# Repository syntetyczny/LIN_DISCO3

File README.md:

##LIN DISCO3 WBus webasto driver

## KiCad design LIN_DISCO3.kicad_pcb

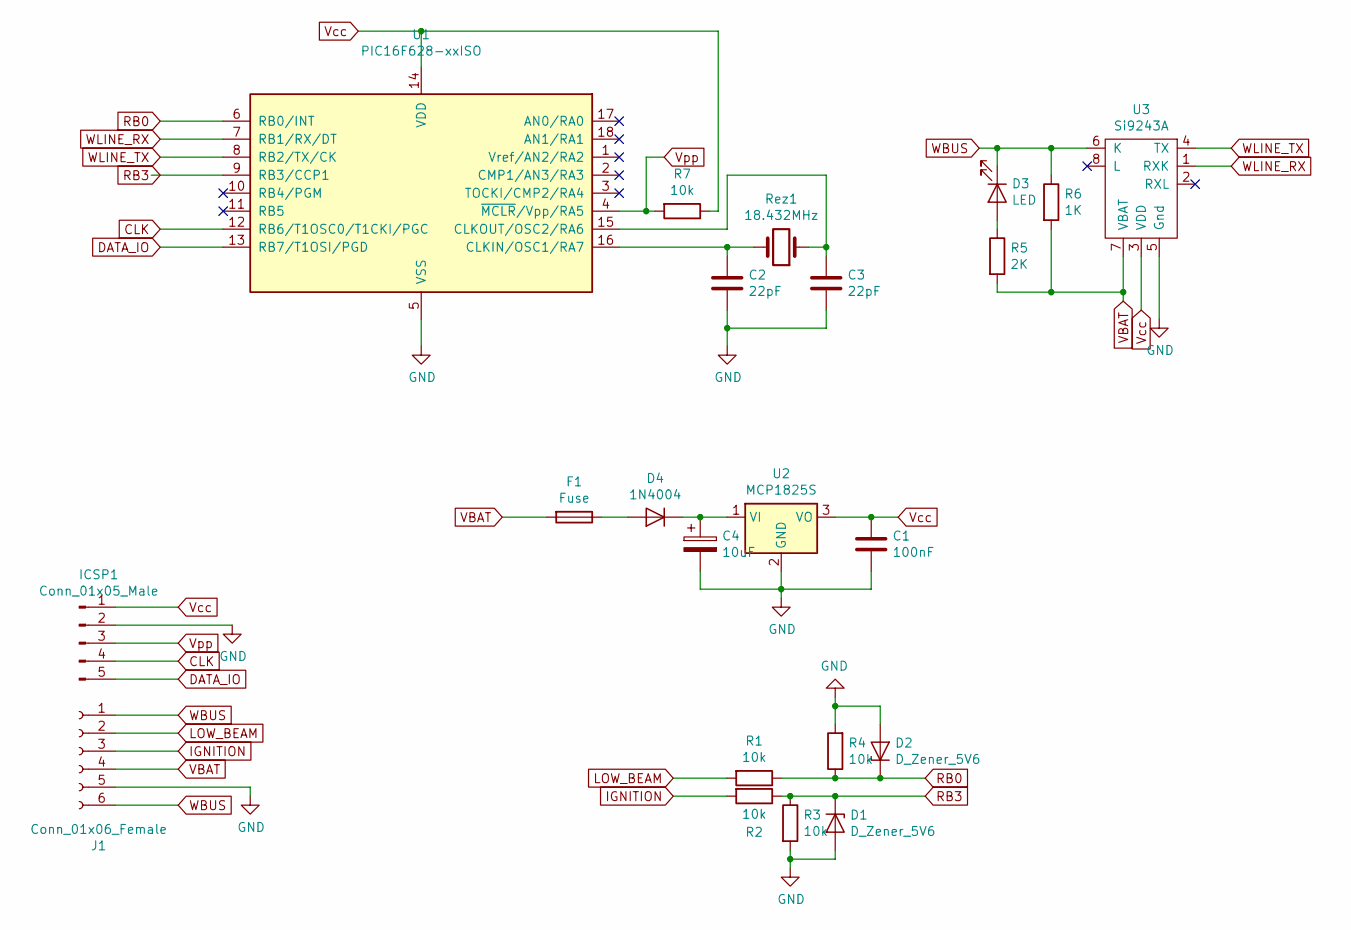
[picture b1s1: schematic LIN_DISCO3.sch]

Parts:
C1: 100nF; C_0805_2012Metric_Pad1.15x1.40mm_HandSolder
C2, C3: 22pF; C_0805_2012Metric_Pad1.15x1.40mm_HandSolder
C4: 10uF; CP_Elec_4x5.8
D1, D2: D_Zener_5V6; D_MiniMELF
D3: LED; LED_0805_2012Metric_Pad1.15x1.40mm_HandSolder
D4: 1N4004; D_SMB
F1: Fuse; Fuseholder_Cylinder-5x20mm_Stelvio-Kontek_PTF78_Horizontal_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
ICSP1: Conn_01x05_Male; PinHeader_1x05_P2.54mm_Vertical
J1: Conn_01x06_Female; TerminalBlock_Phoenix_PT-1,5-6-5.0-H_1x06_P5.00mm_Horizontal
R1, R2, R3, R4, R7: 10k; R_0805_2012Metric_Pad1.15x1.40mm_HandSolder
R5: 2K; R_0805_2012Metric_Pad1.15x1.40mm_HandSolder
R6: 1K; R_0805_2012Metric_Pad1.15x1.40mm_HandSolder
Rez1: 18.432MHz; Crystal_HC49-U_Vertical
U1: PIC16F628-xxISO; SOIC-18W_7.5x11.6mm_P1.27mm
U2: MCP1825S; SOT-223-3_TabPin2
U3: Si9243A; SOIC-8_3.9x4.9mm_P1.27mm

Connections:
CLK: ICSP1.4, U1.12 (RB6/T1OSC0/T1CKI/PGC)
DATA_IO: ICSP1.5, U1.13 (RB7/T1OSI/PGD)
GND: C1.2, C2.2, C3.2, C4.2, D1.2 (A), D2.2 (A), ICSP1.2, J1.5, R3.2, R4.2, U1.5 (VSS), U2.2 (GND), U3.5 (Gnd)
IGNITION: J1.3, R2.2
LOW_BEAM: J1.2, R1.2
unnamed: C2.1, Rez1.2, U1.16 (CLKIN/OSC1/RA7)
unnamed: C3.1, Rez1.1, U1.15 (CLKOUT/OSC2/RA6)
unnamed: C4.1, D4.1 (K), U2.1 (VI)
unnamed: D3.2 (A), R5.1
unnamed: D4.2 (A), F1.1
RB0: D2.1 (K), R1.1, R4.1, U1.6 (RB0/INT)
RB3: D1.1 (K), R2.1, R3.1, U1.9 (RB3/CCP1)
VBAT: F1.2, J1.4, R5.2, R6.2, U3.7 (VBAT)
Vcc: C1.1, ICSP1.1, R7.1, U1.14 (VDD), U2.3 (VO), U3.3 (VDD)
Vpp: ICSP1.3, R7.2, U1.4 (~MCLR~/Vpp/RA5)
WBUS: D3.1 (K), J1.1, J1.6, R6.1, U3.6 (K)
WLINE_RX: U1.7 (RB1/RX/DT), U3.1 (RXK)
WLINE_TX: U1.8 (RB2/TX/CK), U3.4 (TX)

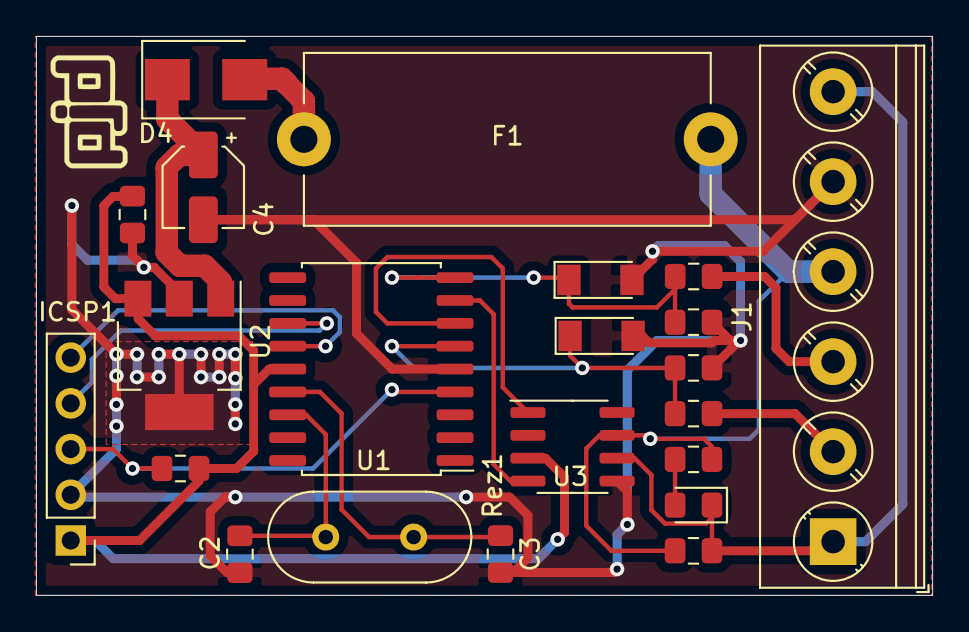
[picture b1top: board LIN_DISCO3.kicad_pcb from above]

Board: 2 copper layers, 49.8 x 31.1 mm, 22 parts (0 on the bottom side), 18 nets.

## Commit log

2022-01-23 shematic and docs init
2022-01-24 schematic: draft
2022-01-26 reroute, added 6p arks
2022-01-26 reroute: voltages
2022-01-26 added ICSP port
2022-02-12 transceiver changed to transistor cascade
2022-02-15 diodes and transistors case changed
2022-02-15 updated board for sot23 and miniMELF
2022-02-15 board layout prepared for production
2022-02-15 Added README.md
2022-03-08 design: update conn added fuse power diode bigger cappacitor
